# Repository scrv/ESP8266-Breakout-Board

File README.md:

# ESP8266 SMD to DIP adapter

A breadboard-friendly adapter for the ESP-12

Find the details at [Hackster.io](https://www.hackster.io/scrv201/esp8266-smd-to-dip-adapter-c3e416)

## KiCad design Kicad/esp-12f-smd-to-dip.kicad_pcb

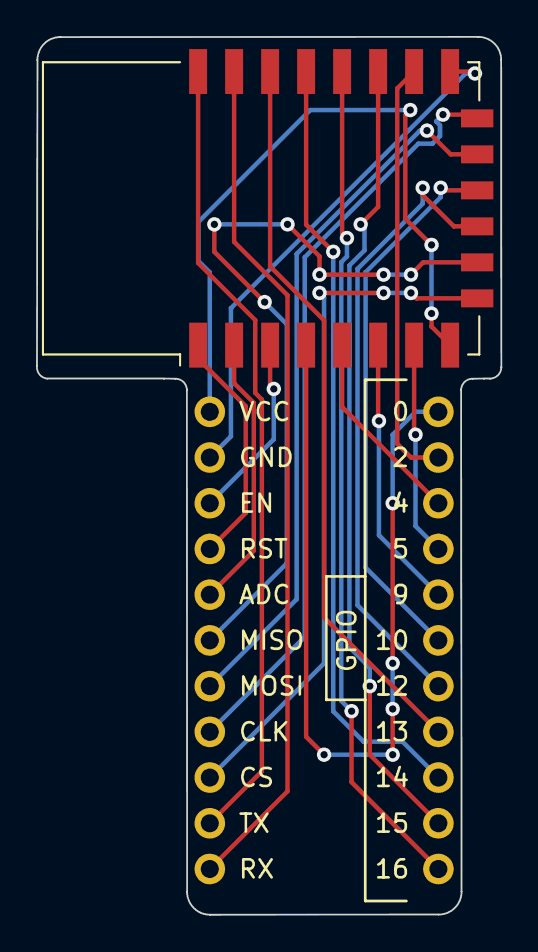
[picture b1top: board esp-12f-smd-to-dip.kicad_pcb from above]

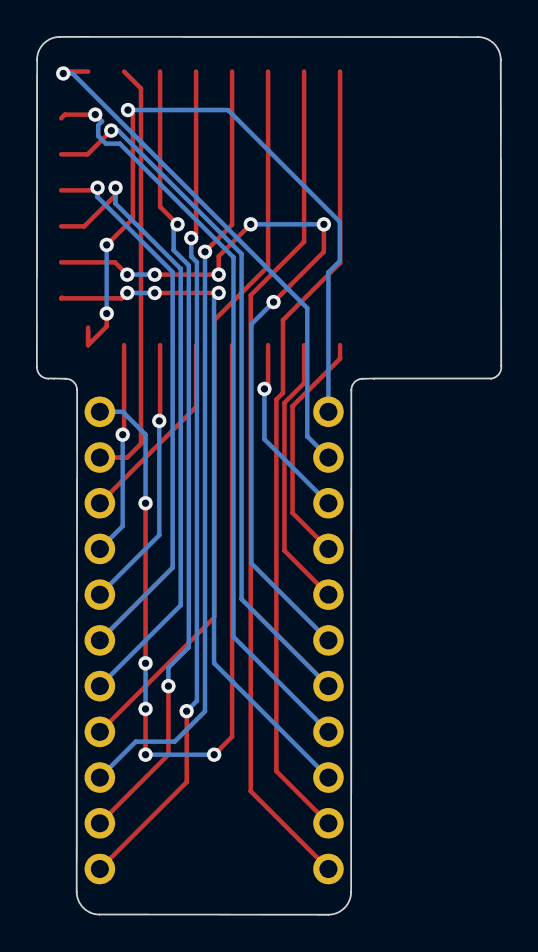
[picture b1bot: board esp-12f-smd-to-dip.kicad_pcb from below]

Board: 2 copper layers, 25.8 x 48.8 mm, 3 parts (2 on the bottom side), 22 nets.

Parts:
J1, J2: Conn_01x11_Male; PinHeader_1x11_P2.54mm_Vertical
U1: ESP-12F; ESP-12E

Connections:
adc: J1.5, U1.2 (ADC)
cs: J1.9, U1.9 (CS0)
en: J1.3, U1.3 (EN)
gnd: J1.2, U1.15 (GND)
gpio0: J2.11, U1.4 (GPIO16)
gpio2: J2.10, U1.16 (GPIO15)
gpio4: J2.9, U1.5 (GPIO14)
gpio5: J2.8, U1.7 (GPIO13)
gpio9: J2.7, U1.6 (GPIO12)
gpio10: J2.6, U1.12 (GPIO10)
gpio12: J2.5, U1.11 (GPIO9)
gpio13: J2.4, U1.20 (GPIO5)
gpio14: J2.3, U1.19 (GPIO4)
gpio15: J2.2, U1.17 (GPIO2)
gpio16: J2.1, U1.18 (GPIO0)
miso: J1.6, U1.10 (MISO)
mosi: J1.7, U1.13 (MOSI)
rst: J1.4, U1.1 (~RST)
rx: J1.11, U1.21 (GPIO3/RXD)
sclk: J1.8, U1.14 (SCLK)
tx: J1.10, U1.22 (GPIO1/TXD)
vcc: J1.1, U1.8 (VCC)

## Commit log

2022-07-24 PCB, Schematic and gerber files upload
2022-07-25 README.md Update
